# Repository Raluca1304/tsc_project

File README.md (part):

# PROIECT TSC OpenBook 
## Nica Mioara-Raluca 334CA 

---

## 1. Diagrama bloc

---

## 2. BOM (Bill Of Materials)

|   Nr. piesa | Nume piesa    | Site                                                                                                                                                                                                                                                | Datasheet                                                                                                                                                                |
|------------:|:--------------|:----------------------------------------------------------------------------------------------------------------------------------------------------------------------------------------------------------------------------------------------------|:-------------------------------------------------------------------------------------------------------------------------------------------------------------------------|
|           1 | BOOT_BUTON    | https://www.snapeda.com/parts/EVQP7L01P/Panasonic%20Electronic%20Components/view-part/?welcome=home                                                                                                                                                 | https://www.snapeda.com/parts/EVQP7L01P/Panasonic/datasheet/                                                                                                             |
|           2 | C1            | https://componentsearchengine.com/part-view/CC0402MRX5R5BB106/YAGEO                                                                                                                                                                                 | https://componentsearchengine.com/Datasheets/2/CC0402MRX5R5BB106.pdf                                                                                                     |
|           3 | C1_BAT        | https://componentsearchengine.com/part-view/CC0402MRX5R5BB106/YAGEO                                                                                                                                                                                 | https://componentsearchengine.com/Datasheets/2/CC0402MRX5R5BB106.pdf                                                                                                     |
|           4 | C1_BAT2       | https://componentsearchengine.com/part-view/CC0402MRX5R5BB106/YAGEO                                                                                                                                                                                 | https://componentsearchengine.com/Datasheets/2/CC0402MRX5R5BB106.pdf                                                                                                     |
|           5 | C2            | https://componentsearchengine.com/part-view/CC0402MRX5R5BB106/YAGEO                                                                                                                                                                                                                                                    |                                                                                                       |
|           6 | C2_BAT        | https://componentsearchengine.com/part-view/CC0402MRX5R5BB106/YAGEO                                                                                                                                                                                                                                                   |                                                                                                        |
|           7 | C3            | https://componentsearchengine.com/part-view/CC0402MRX5R5BB106/YAGEO                                                                                                                                                                                                                                                    |                                                                                                       |
|           8 | C4            | https://componentsearchengine.com/part-view/CC0402MRX5R5BB106/YAGEO                                                                                                                                                                                                                                                    |                                                                                                       |
|           9 | C4_USB        | https://componentsearchengine.com/part-view/CC0402MRX5R5BB106/YAGEO                                                                                                                                                                                                                                                    |                                                                                                       |
|          10 | C5            | https://componentsearchengine.com/part-view/CC0402MRX5R5BB106/YAGEO                                                                                                                                                                                                                                                    |                                                                                                       |
|          11 | C5_USB        | https://componentsearchengine.com/part-view/CC0402MRX5R5BB106/YAGEO                                                                                                                                                                                                                                                    |                                                                                                       |
|          12 | C6            | https://componentsearchengine.com/part-view/CC0402MRX5R5BB106/YAGEO                                                                                                                                                                                                                                                     |                                                                                                      |
|          13 | C7            | https://componentsearchengine.com/part-view/CC0402MRX5R5BB106/YAGEO                                                                                                                                                                                                                                                     |                                                                                                      |
|          14 | C8            | https://componentsearchengine.com/part-view/CC0402MRX5R5BB106/YAGEO                                                                                                                                                                                                                                                    |                                                                                                       |
|          15 | C9            | https://componentsearchengine.com/part-view/CC0402MRX5R5BB106/YAGEO                                                                                                                                                                                                                                                     |                                                                                                      |
|          16 | C10           | https://industry.panasonic.com/global/en/products/control/switch/light-touch/number/evqpuj02k                                                                                                                                                       | https://industry.panasonic.com/global/en/downloads?tab=catalog&small_g_cd=203&part_no=EVQPUJ02K                                                                          |
|          17 | C10_SUPERCAR  | https://industry.panasonic.com/global/en/products/control/switch/light-touch/number/evqpuj02k                                                                                                                                                       | https://industry.panasonic.com/global/en/downloads?tab=catalog&small_g_cd=203&part_no=EVQPUJ02K                                                                          |
|          18 | CHANGE_BUTTON | https://www.snapeda.com/parts/EVQP7L01P/Panasonic%20Electronic%20Components/view-part/?welcome=home                                                                                                                                                 | https://www.snapeda.com/parts/EVQP7L01P/Panasonic/datasheet/                                                                                                             |
|          19 | C_DELAY       | https://componentsearchengine.com/part-view/CC0402MRX5R5BB106/YAGEO                                                                                                                                                                                 | https://componentsearchengine.com/Datasheets/2/CC0402MRX5R5BB106.pdf                                                                                                     |
|          20 | D1            | https://www.snapeda.com/parts/USBLC6-2SC6Y/STMicroelectronics/view-part/?ref=eda                                                                                                                                                                    | https://www.snapeda.com/parts/USBLC6-2SC6Y/STMicroelectronics/view-part/?ref=eda                                                                                         |
|          21 | D2            | https://ro.mouser.com/ProductDetail/KYOCERA-AVX/SD0805S020S1R0?qs=jCA%252BPfw4LHbpkAoSnwrdjw%3D%3D                                                                                                                                                  | https://ro.mouser.com/datasheet/2/40/schottky-3165252.pdf                                                                                                                |
|          22 | D3            | https://ro.mouser.com/ProductDetail/KYOCERA-AVX/SD0805S020S1R0?qs=jCA%252BPfw4LHbpkAoSnwrdjw%3D%3D                                                                                                                                                                                                                                                     |                                                                       |
|          23 | D4            | https://ro.mouser.com/ProductDetail/KYOCERA-AVX/SD0805S020S1R0?qs=jCA%252BPfw4LHbpkAoSnwrdjw%3D%3D                                                                                                                                                                                                                                                    |                                                                        |
|          24 | D5            | https://ro.mouser.com/ProductDetail/KYOCERA-AVX/SD0805S020S1R0?qs=jCA%252BPfw4LHbpkAoSnwrdjw%3D%3D                                                                                                                                                                                                                                                     |                                                                       |
|          25 | D6            | https://www.snapeda.com/parts/PGB1010603MR/Littelfuse/view-part/?ref=eda                                                                                                                                                                            | https://www.snapeda.com/parts/PGB1010603MR/Littelfuse%20Inc./datasheet/                                                                                                  |
|          26 | D7            | https://ro.mouser.com/ProductDetail/KYOCERA-AVX/SD0805S020S1R0?qs=jCA%252BPfw4LHbpkAoSnwrdjw%3D%3D                                                                                                                                                  | https://ro.mouser.com/datasheet/2/40/schottky-3165252.pdf                                                                                                                |
|          27 | D8            | https://www.snapeda.com/parts/PGB1010603MR/Littelfuse/view-part/?ref=eda                                                                                                                                                                            | https://www.snapeda.com/parts/PGB1010603MR/Littelfuse%20Inc./datasheet/                                                                                                  |
|          28 | D9            | https://www.snapeda.com/parts/PGB1010603MR/Littelfuse/view-part/?ref=eda                                                                                                                                                                                                                                                   |                                                                                                   |
|          29 | D10           | https://www.snapeda.com/parts/PGB1010603MR/Littelfuse/view-part/?ref=eda                                                                                                                                                                                                                                                    |                                                                                                  |
|          30 | D11           | https://www.snapeda.com/parts/PGB1010603MR/Littelfuse/view-part/?ref=eda                                                                                                                                                                                                                                                     |                                                                                                 |
|          31 | D12           | https://www.snapeda.com/parts/PGB1010603MR/Littelfuse/view-part/?ref=eda                                                                                                                                                                                                                                                    |                                                                                                  |
|          32 | EPD_C1        | https://componentsearchengine.com/part-view/CC0402MRX5R5BB106/YAGEO                                                                                                                                                                                 | https://componentsearchengine.com/Datasheets/2/CC0402MRX5R5BB106.pdf                                                                                                     |
|          33 | EPD_C2        | https://componentsearchengine.com/part-view/CC0402MRX5R5BB106/YAGEO                                                                                                                                                                                 | https://componentsearchengine.com/Datasheets/2/CC0402MRX5R5BB106.pdf                                                                                                     |
|          34 | EPD_C5        | https://componentsearchengine.com/part-view/CC0402MRX5R5BB106/YAGEO                                                                                                                                                                                 | https://componentsearchengine.com/Datasheets/2/CC0402MRX5R5BB106.pdf                                                                                                     |
|          35 | EPD_C6        | https://componentsearchengine.com/part-view/CC0402MRX5R5BB106/YAGEO                                                                                                                                                                                 | https://componentsearchengine.com/Datasheets/2/CC0402MRX5R5BB106.pdf                                                                                                     |
|          36 | EPD_C7        | https://componentsearchengine.com/part-view/CC0402MRX5R5BB106/YAGEO                                                                                                                                                                                 | https://componentsearchengine.com/Datasheets/2/CC0402MRX5R5BB106.pdf                                                                                                     |
|          37 | EPD_C8        | https://componentsearchengine.com/part-view/CC0402MRX5R5BB106/YAGEO                                                                                                                                                                                 | https://componentsearchengine.com/Datasheets/2/CC0402MRX5R5BB106.pdf                                                                                                     |
|          38 | EPD_C9        | https://componentsearchengine.com/part-view/CC0402MRX5R5BB106/YAGEO                                                                                                                                                                                 | https://componentsearchengine.com/Datasheets/2/CC0402MRX5R5BB106.pdf                                                                                                     |
|          39 | EPD_C10       | https://componentsearchengine.com/part-view/CC0402MRX5R5BB106/YAGEO                                                                                                                                                                                 | https://componentsearchengine.com/Datasheets/2/CC0402MRX5R5BB106.pdf                                                                                                     |
|          40 | EPD_C11       | https://componentsearchengine.com/part-view/CC0402MRX5R5BB106/YAGEO                                                                                                                                                                                 | https://componentsearchengine.com/Datasheets/2/CC0402MRX5R5BB106.pdf                                                                                                     |
|          41 | EPD_C12       | https://componentsearchengine.com/part-view/CC0402MRX5R5BB106/YAGEO                                                                                                                                                                                 | https://componentsearchengine.com/Datasheets/2/CC0402MRX5R5BB106.pdf                                                                                                     |
|          42 | IC1           | https://componentsearchengine.com/part-view/BD5229G-TR/ROHM%20Semiconductor                                                                                                                                                                         | https://datasheet.datasheetarchive.com/originals/distributors/Datasheets_SAMA/f2b9741ef86007909f138d561a359946.pdf                                                       |
|          43 | IC4           | https://componentsearchengine.com/part-view/XC6220A331MR-G/Torex                                                                                                                                                                                    | https://product.torexsemi.com/system/files/series/xc6220.pdf                                                                                                             |
|          44 | J1            | https://componentsearchengine.com/part-view/FH34SRJ-24S-0.5SH(99)/Hirose                                                                                                                                                                            | https://www.hirose.com/en/product/document?clcode=CL0580-1255-6-99&productname=FH34SRJ-24S-0.5SH(99)&series=FH34SRJ&documenttype=2DDrawing&lang=en&documentid=0000990903 |
|          45 | J2            | https://componentsearchengine.com/part-view/USB4110-GF-A/GCT%20(GLOBAL%20CONNECTOR%20TECHNOLOGY)                                                                                                                                                    | https://gct.co/files/drawings/usb4110.pdf                                                                                                                                |
|          46 | J3            | https://www.snapeda.com/parts/PRT-14417/SparkFun/view-part/                                                                                                                                                                                         | https://www.snapeda.com/parts/PRT-14417/SparkFun%20Electronics/datasheet/                                                                                                |
|          47 | J4            | https://www.snapeda.com/parts/112A-TAAR-R03/Attend/view-part/                                                                                                                                                                                       | https://www.snapeda.com/parts/112A-TAAR-R03/Attend/datasheet/                                                                                                            |
|          48 | MCP73831      | https://ro.mouser.com/ProductDetail/Microchip-Technology/MCP73831T-2ACI-OT?qs=yUQqVecv4qvbBQBGbHx0Mw%3D%3D&utm_id=20109199409&utm_source=google&utm_medium=cpc&utm_marketing_tactic=emeacorp&gad_source=1&gbraid=0AAAAADn_wf0-USzm1eg1ywGvQg_qMgG3H | https://ro.mouser.com/datasheet/2/268/MCP73831_Family_Data_Sheet_DS20001984H-3441711.pdf                                                                                 |
|          49 | L1            | https://ro.mouser.com/ProductDetail/Wurth-Elektronik/744043680?qs=PGXP4M47uW6VkZq%252BkzjrHA%3D%3D                                                                                                                                                  | https://www.we-online.com/components/products/datasheet/744043680.pdf                                                                                                    |
|          50 | PFMF.050.1    | https://ro.mouser.com/ProductDetail/EPCOS-TDK/B72520T0350K062?qs=dEfas%2FXlABIszF52uu7vrg%3D%3D                                                                                                                                                     | https://www.tdk-electronics.tdk.com/inf/75/db/CTVS_14/Surge_protection_series.pdf                                                                                        |
|          51 | Q1            | https://componentsearchengine.com/part-view/DMG2305UX-7/Diodes%20Incorporated                                                                                                                                                                       | https://www.diodes.com//assets/Datasheets/DMG2305UX.pdf                                                                                                                  |
|          52 | Q2            | https://componentsearchengine.com/part-view/DMG2305UX-7/Diodes%20Incorporated                                                                                                                                                                                                                                                     |                                                                                            |
|          53 | Q3            | https://componentsearchengine.com/part-view/SI1308EDL-T1-GE3/Vishay                                                                                                                                                                                 | https://componentsearchengine.com/part-view/SI1308EDL-T1-GE3/Vishay                                                                                                      |
|          54 | R1            | https://componentsearchengine.com/part-view/R0402%201%25%20100%20K%20(RC0402FR-07100KL)/YAGEO                                                                                                                                                       | https://www.yageo.com/upload/media/product/products/datasheet/rchip/PYu-RC_Group_51_RoHS_L_12.pdf                                                                        |
|          55 | R1_PINH       | https://componentsearchengine.com/part-view/R0402%201%25%20100%20K%20(RC0402FR-07100KL)/YAGEO                                                                                                                                                       | https://www.yageo.com/upload/media/product/products/datasheet/rchip/PYu-RC_Group_51_RoHS_L_12.pdf                                                                        |
|          56 | R1_PINH1      | https://componentsearchengine.com/part-view/R0402%201%25%20100%20K%20(RC0402FR-07100KL)/YAGEO                                                                                                                                                       | https://www.yageo.com/upload/media/product/products/datasheet/rchip/PYu-RC_Group_51_RoHS_L_12.pdf                                                                        |
|          57 | R1_BAT        | https://componentsearchengine.com/part-view/R0402%201%25%20100%20K%20(RC0402FR-07100KL)/YAGEO                                                                                                                                                       | https://www.yageo.com/upload/media/product/products/datasheet/rchip/PYu-RC_Group_51_RoHS_L_12.pdf                                                                        |
|          58 | R1_PWRUSB     | https://componentsearchengine.com/part-view/R0402%201%25%20100%20K%20(RC0402FR-07100KL)/YAGEO                                                                                                                                                       | https://www.yageo.com/upload/media/product/products/datasheet/rchip/PYu-RC_Group_51_RoHS_L_12.pdf                                                                        |
|          59 | R2            | https://componentsearchengine.com/part-view/R0402%201%25%20100%20K%20(RC0402FR-07100KL)/YAGEO                                                            |                                                                                                                                                                          |
|          60 | R2_PINH       | https://componentsearchengine.com/part-view/R0402%201%25%20100%20K%20(RC0402FR-07100KL)/YAGEO                                                            |                                                                                                                                                                          |
|          61 | R2-PINH1      | https://componentsearchengine.com/part-view/R0402%201%25%20100%20K%20(RC0402FR-07100KL)/YAGEO                                                            |                                                                                                                                                                          |
|          62 | R2            | https://componentsearchengine.com/part-view/R0402%201%25%20100%20K%20(RC0402FR-07100KL)/YAGEO                                                            |                                                                                                                                                                          |
|          63 | R2-PINH       | https://componentsearchengine.com/part-view/R0402%201%25%20100%20K%20(RC0402FR-07100KL)/YAGEO                                                            |                                                                                                                                                                          |
|          64 | R2-PINH1      | https://componentsearchengine.com/part-view/R0402%201%25%20100%20K%20(RC0402FR-07100KL)/YAGEO                                                            |                                                                                                                                                                          |
|          65 | R2_USB        | https://componentsearchengine.com/part-view/R0402%201%25%20100%20K%20(RC0402FR-07100KL)/YAGEO                                                            |                                                                                                                                                                          |
|          66 | R2_USB        | https://componentsearchengine.com/part-view/R0402%201%25%20100%20K%20(RC0402FR-07100KL)/YAGEO                                                            |                                                                                                                                                                          |
|          67 | R2_USB1       | https://componentsearchengine.com/part-view/R0402%201%25%20100%20K%20(RC0402FR-07100KL)/YAGEO                                                            |                                                                                                                                                                          |
|          68 | R3            | https://componentsearchengine.com/part-view/R0402%201%25%20100%20K%20(RC0402FR-07100KL)/YAGEO                                                            |                                                                                                                                                                          |
|          69 | R4            | https://componentsearchengine.com/part-view/R0402%201%25%20100%20K%20(RC0402FR-07100KL)/YAGEO                                                            |                                                                                                                                                                          |
|          70 | R5            | https://componentsearchengine.com/part-view/R0402%201%25%20100%20K%20(RC0402FR-07100KL)/YAGEO                                                            |                                                                                                                                                                          |
|          71 | R6            | https://componentsearchengine.com/part-view/R0402%201%25%20100%20K%20(RC0402FR-07100KL)/YAGEO                                                            |                                                                                                                                                                          |
|          72 | R7            | https://componentsearchengine.com/part-view/R0402%201%25%20100%20K%20(RC0402FR-07100KL)/YAGEO                                                            |                                                                                                                                                                          |
|          73 | R8            | https://componentsearchengine.com/part-view/R0402%201%25%20100%20K%20(RC0402FR-07100KL)/YAGEO                                                            |                                                                                                                                                                          |
|          74 | R9            | https://componentsearchengine.com/part-view/R0402%201%25%20100%20K%20(RC0402FR-07100KL)/YAGEO                                                            |                                                                                                                                                                          |
|          75 | R10           | https://componentsearchengine.com/part-view/R0402%201%25%20100%20K%20(RC0402FR-07100KL)/YAGEO                                                            |                                                                                                                                                                          |
|          76 | RESET_BUTTON  | https://www.snapeda.com/parts/EVQP7L01P/Panasonic%20Electronic%20Components/view-part/?welcome=home                                                                                                                                                 | https://www.snapeda.com/parts/EVQP7L01P/Panasonic/datasheet/                                                                                                             |
|          77 | R_BOOT        | https://componentsearchengine.com/part-view/R0402%201%25%20100%20K%20(RC0402FR-07100KL)/YAGEO                                                                                                                                                       | https://www.yageo.com/upload/media/product/products/datasheet/rchip/PYu-RC_Group_51_RoHS_L_12.pdf                                                                        |
|          78 | R_CAPACITOR   | https://componentsearchengine.com/part-view/R0402%201%25%20100%20K%20(RC0402FR-07100KL)/YAGEO                                                                                                                                                       | https://www.yageo.com/upload/media/product/products/datasheet/rchip/PYu-RC_Group_51_RoHS_L_12.pdf                                                                        |
|          79 | R_CHANGE      | https://componentsearchengine.com/part-view/R0402%201%25%20100%20K%20(RC0402FR-07100KL)/YAGEO                                                                                                                                                       | https://www.yageo.com/upload/media/product/products/datasheet/rchip/PYu-RC_Group_51_RoHS_L_12.pdf                                                                        |
|          80 | R_CL1         | https://componentsearchengine.com/part-view/R0402%201%25%20100%20K%20(RC0402FR-07100KL)/YAGEO                                                                                                                                                       | https://www.yageo.com/upload/media/product/products/datasheet/rchip/PYu-RC_Group_51_RoHS_L_12.pdf                                                                        |
|          81 | R_RESET       | https://componentsearchengine.com/part-view/R0402%201%25%20100%20K%20(RC0402FR-07100KL)/YAGEO                                                                                                                                                       | https://www.yageo.com/upload/media/product/products/datasheet/rchip/PYu-RC_Group_51_RoHS_L_12.pdf                                                                        |
|          82 | SENSOR2       | https://www.snapeda.com/parts/BME680/Bosch/view-part/?welcome=home                                                                                                                                                                                  | https://www.snapeda.com/parts/BME680/Bosch%20Sensortec/datasheet/                                                                                                        |
|          83 | SJ1           | https://grabcad.com/library/solder-jumpers-1                                                                                                                                                                                                        | https://grabcad.com/library/solder-jumpers-1                                                                                                                             |
|          84 | TP1           | Am folosit aici model 3D personalizat realizat de mine                                                                                                                                                                                              |                                                                                                                                                                          |
|          85 | TP2           |                                                                                                                                                                                                                                                     |                                                                                                                                                                          |
|          86 | TP3           |                                                                                                                                                                                                                                                     |                                                                                                                                                                          |
|          87 | TP4           |                                                                                                                                                                                                                                                     |                                                                                                                                                                          |
|          88 | TP5           |                                                                                                                                                                                                                                                     |                                                                                                                                                                          |
|          89 | TP6           |                                                                                                                                                                                                                                                     |                                                                                                                                                                          |
|          90 | TP7           |                                                                                                                                                                                                                                                     |                                                                                                                                                                          |
|          91 | TP8           |                                                                                                                                                                                                                                                     |                                                                                                                                                                          |
|          92 | TP9           |                                                                                                                                                                                                                                                     |                                                                                                                                                                          |
|          93 | TP10          |                                                                                                                                                                                                                                                     |                                                                                                                                                                          |
|          94 | TP11          |                                                                                                                                                                                                                                                     |                                                                                                                                                                          |
|          95 | TP12          |                                                                                                                                                                                                                                                     |                                                                                                                                                                          |
|          96 | TP13          |                                                                                                                                                                                                                                                     |                                                                                                                                                                          |
|          97 | TP14          |                                                                                                                                                                                                                                                     |                                                                                                                                                                          |
|          98 | TP15          |                                                                                                                                                                                                                                                     |                                                                                                                                                                          |
|          99 | TP16          |                                                                                                                                                                                                                                                     |                                                                                                                                                                          |
|         100 | TP17          |                                                                                                                                                                                                                                                     |                                                                                                                                                                          |
|         101 | U1            | https://www.snapeda.com/parts/W25Q512JVEIQ/Winbond+Electronics/view-part/?ref=eda                                                                                                                                                                   | https://www.snapeda.com/parts/W25Q512JVEIQ/Winbond+Electronics/view-part/?ref=eda                                                                                        |
|         102 | U2            | https://www.snapeda.com/parts/ESP32-C6-WROOM-1-N8/Espressif+Systems/view-part/?ref=eda                                                                                                                                                              | https://www.snapeda.com/parts/ESP32-C6-WROOM-1-N8/Espressif%20Systems/datasheet/                                                                                         |
|         103 | U3            | https://www.snapeda.com/parts/DS3231SN%23/Analog+Devices/view-part/?ref=eda                                                                                                                                                                         | https://www.snapeda.com/parts/DS3231SN%23/Analog%20Devices/datasheet/                                                                                                    |
|         104 | U4            | https://www.snapeda.com/parts/MAX17048G+T10/Analog+Devices/view-part/?ref=eda                                                                                                                                                                       | https://www.snapeda.com/parts/MAX17048G+T10/Analog%20Devices/datasheet/                                                                                                  |

---

## 3. Descriere hardware

Proiectul OpenBook este un sistem portabil de monitorizare ambientala cu microcontroller ESP32-C6. Acesta comunica cu senzori, memorie externa si un ecran E-Ink pentru afisare. Dispozitivul este alimentat prin USB-C sau baterie Li-Po, avand management de energie eficient.

- ESP32-C6 WROOM este creierul central si comunica prin:
  - SPI: SD Card, Flash, E-Ink
  - I2C: BME688, RTC, MAX17048
  - UART: MH-Z19B, PMSA003
  - GPIO: butoane, test pads, control display

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
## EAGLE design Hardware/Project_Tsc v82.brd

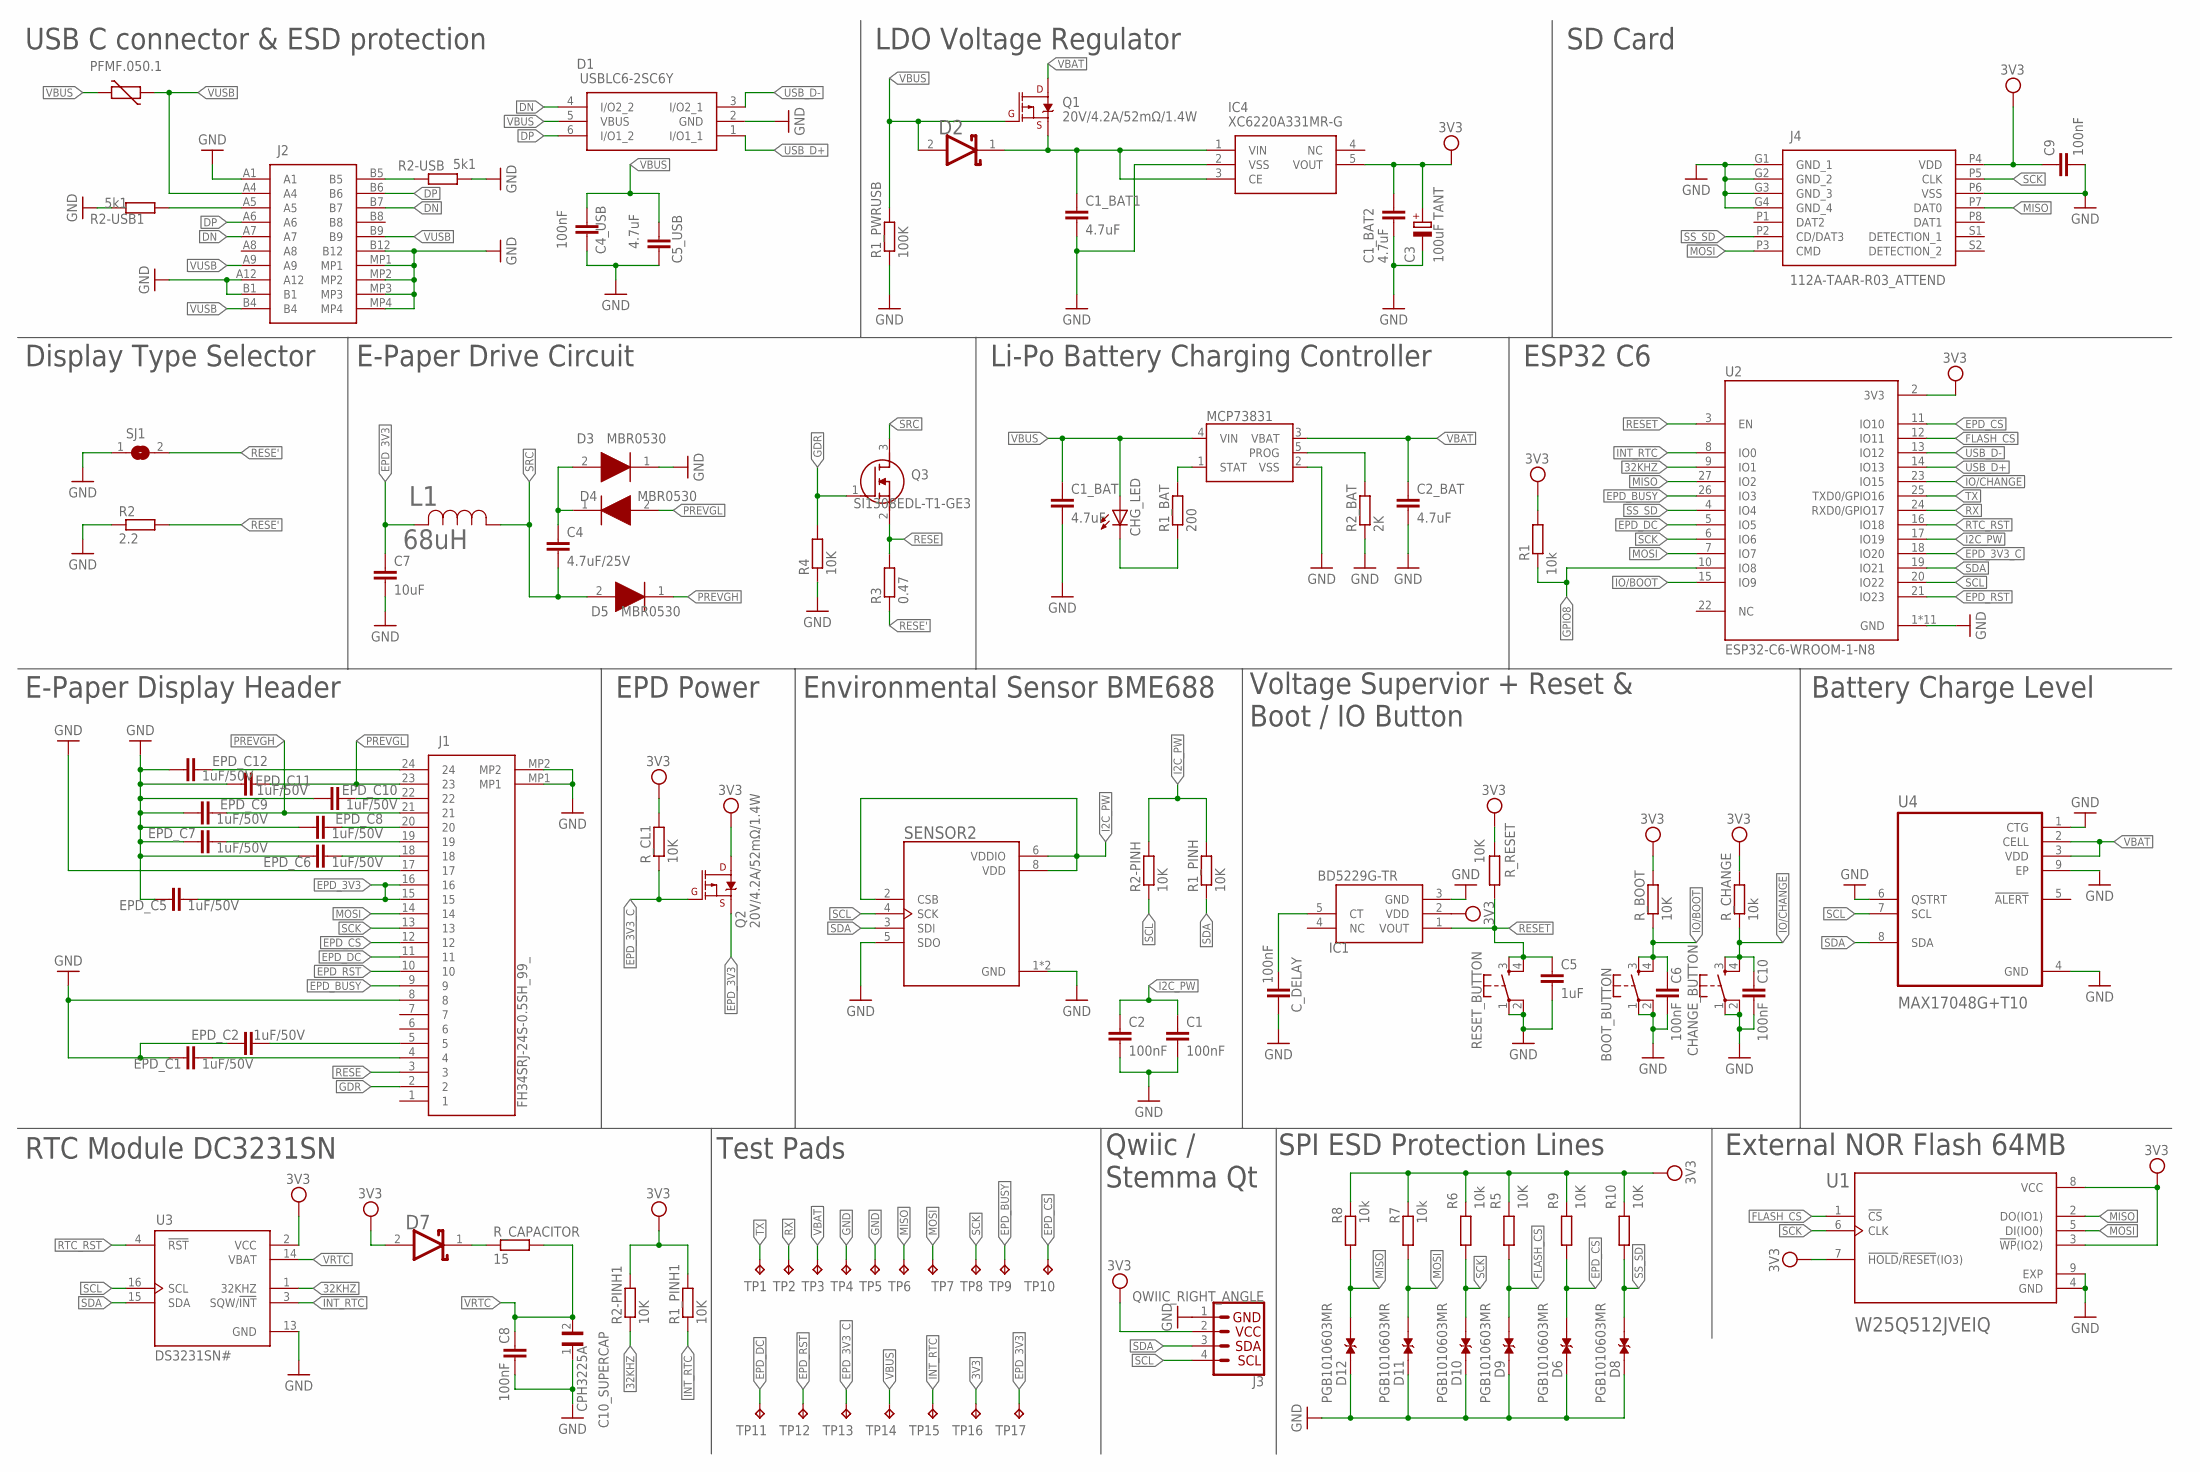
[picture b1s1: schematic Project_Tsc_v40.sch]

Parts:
BOOT_BUTTON: BUTTON_CUSYOMV1; MYBUTTON
C1, C2, C6, C9, C10: 100nF; EAGLE-LTSPICE_C0402
C1_BAT, C1_BAT1, C1_BAT2, C2_BAT, C5_USB: 4.7uF; ESP32_WROVER_EAGLE-LTSPICE_C0402
C3: 100uF TANT; RCL_CT3528
C4: 4.7uF/25V; ESP32_WROVER_EAGLE-LTSPICE_C0402
C4_USB, C8: 100nF; ESP32_WROVER_EAGLE-LTSPICE_C0402
C5: 1uF; EAGLE-LTSPICE_C0402
C7: 10uF; EAGLE-LTSPICE_C0402
C10_SUPERCAP: CPH3225A; CAPCP3225X100N
CHANGE_BUTTON: BUTTON_CUSYOMV1; MYBUTTON
CHG_LED: ADAFRUIT_LEDCHIP-LED0603; ADAFRUIT_CHIP-LED0603
C_DELAY: 100nF; ESP32_WROVER_EAGLE-LTSPICE_C0402
D1: USBLC6-2SC6Y; SOT95P280X145-6N
D2, D7: ESP32_WROVER_AVX---SD0805S020S1R0_AVX_SD0805S020S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; ESP32_WROVER_AVX---SD0805S020S1R0_AVX_SD0805S020S1R0_0
D3, D4, D5: MBR0530; SOD3716X135N
D6, D8, D9, D10, D11, D12: PGB1010603MR; DIOC1608X36N
EPD_C1, EPD_C2, EPD_C5, EPD_C6, EPD_C7, EPD_C8, EPD_C9, EPD_C10, EPD_C11, EPD_C12: 1uF/50V; EAGLE-LTSPICE_C0402
IC1: BD5229G-TR; SOT95P280X125-5N
IC4: XC6220A331MR-G; SOT95P280X120-5N
J1: FH34SRJ-24S-0.5SH_99_; FH34SRJ24S05SH99
J2: SAMACSYS_PARTS_USB4110-GF-A; SAMACSYS_PARTS_USB4110GFA
J3: QWIIC_RIGHT_ANGLE; JST04_1MM_RA
J4: 112A-TAAR-R03_ATTEND; 112ATAARR03ATTEND
L1: 68uH; IND_4828-WE-TPC_WRE
MCP73831: ESP32_WROVER_SPARKFUN-IC-POWER_MCP73831; ESP32_WROVER_SPARKFUN-IC-POWER_SOT23-5
PFMF.050.1: ESP32C6_VARISTORCN1812; ESP32C6_VARISTOR_CT/CN1812
Q1, Q2: 20V/4.2A/52mΩ/1.4W; ESP32_WROVER_SPARKFUN-DISCRETESEMI_SOT23-3
Q3: SI1308EDL-T1-GE3; SOT65P210X110-3N
R1, R6, R7, R8: 10k; ESP32_WROVER_EAGLE-LTSPICE_R0402
R1_BAT: 200; ESP32_WROVER_EAGLE-LTSPICE_R0402
R1_PINH, R1_PINH1, R2-PINH, R2-PINH1, R4, R5, R9, R10: 10K; ESP32_WROVER_EAGLE-LTSPICE_R0402
R1_PWRUSB: 100K; ESP32_WROVER_EAGLE-LTSPICE_R0402
R2: 2.2; ESP32_WROVER_EAGLE-LTSPICE_R0402
R2-USB, R2-USB1: 5k1; ESP32_WROVER_EAGLE-LTSPICE_R0402
R2_BAT: 2K; ESP32_WROVER_EAGLE-LTSPICE_R0402
R3: 0.47; ESP32_WROVER_EAGLE-LTSPICE_R0402
RESET_BUTTON: BUTTON_CUSYOMV1; MYBUTTON
R_BOOT: 10K; ESP32_WROVER_EAGLE-LTSPICE_R0402
R_CAPACITOR: 15; ESP32_WROVER_EAGLE-LTSPICE_R0402
R_CHANGE: 10k; ESP32_WROVER_EAGLE-LTSPICE_R0402
R_CL1: 10K; ESP32_WROVER_EAGLE-LTSPICE_R0402
R_RESET: 10K; ESP32_WROVER_EAGLE-LTSPICE_R0402
SENSOR2: ESP32_WROVER_BME680_BME680; ESP32_WROVER_BME680_PSON80P300X300X100-8N
SJ1: SJ
TP1, TP2, TP3, TP4, TP5, TP6, TP7, TP8, TP9, TP10, TP11, TP12, TP13, TP14, TP15, TP16, TP17: TPTP20R; TP20R
U1: W25Q512JVEIQ; SON127P600X800X80-9N
U2: ESP32-C6-WROOM-1-N8; XCVR_ESP32-C6-WROOM-1-N8
U3: DS3231SN#; SOIC127P1032X265-16N
U4: MAX17048G+T10; SON50P200X200X80-9N

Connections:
3V3: C1_BAT2.1, C3.+, C9.1, D7.2 (ANODE), IC1.2 (VDD), IC4.5 (VOUT), J3.2, J4.P4 (VDD), Q2.3 (D), R1.2, R1_PINH1.2, R2-PINH1.2, R5.2, R6.2, R7.2, R8.2, R9.2, R10.2, R_BOOT.2, R_CHANGE.2, R_CL1.2, R_RESET.2, TP16.TP, U1.3 (!WP!(IO2)), U1.7 (!HOLD!/!RESET!(IO3)), U1.8 (VCC), U2.2 (3V3), U3.2 (VCC)
32KHZ: R2-PINH1.1, U2.9 (IO1), U3.1 (32KHZ)
DN: D1.4 (I/O2_2), J2.A7, J2.B7
DP: D1.6 (I/O1_2), J2.A6, J2.B6
EPD_3V3: C7.1, EPD_C5.2, J1.15, J1.16, L1.2, Q2.2 (S), TP17.TP
EPD_3V3_C: Q2.1 (G), R_CL1.1, TP13.TP, U2.18 (IO20)
EPD_BUSY: J1.9, TP9.TP, U2.26 (IO3)
EPD_CS: D6.1, J1.12, R9.1, TP10.TP, U2.11 (IO10)
EPD_DC: J1.11, TP11.TP, U2.5 (IO5)
EPD_RST: J1.10, TP12.TP, U2.21 (IO23)
FLASH_CS: D9.1, R5.1, U1.1 (!CS), U2.12 (IO11)
GDR: J1.2, Q3.1 (G), R4.2
GND: BOOT_BUTTON.1, BOOT_BUTTON.2, C1.2, C1_BAT.2, C1_BAT1.2, C1_BAT2.2, C2.2, C2_BAT.2, C3.-, C4_USB.2, C5.2, C5_USB.2, C6.2, C7.2, C8.2, C9.2, C10.2, C10_SUPERCAP.1, CHANGE_BUTTON.1, CHANGE_BUTTON.2, C_DELAY.2, D1.2 (GND), D3.1 (K), D6.2, D8.2, D9.2, D10.2, D11.2, D12.2, EPD_C1.1, EPD_C2.1, EPD_C5.1, EPD_C6.1, EPD_C7.1, EPD_C8.1, EPD_C9.1, EPD_C10.1, EPD_C11.1, EPD_C12.1, IC1.3 (GND), IC4.2 (VSS), J1.8, J1.17, J1.MP1, J1.MP2, J2.A1, J2.A12, J2.B1, J2.B12, J2.MP1, J2.MP2, J2.MP3, J2.MP4, J3.1, J4.G1 (GND_1), J4.G2 (GND_2), J4.G3 (GND_3), J4.G4 (GND_4), J4.P6 (VSS), MCP73831.2 (VSS), R1_PWRUSB.1, R2.1, R2-USB.2, R2-USB1.1, R2_BAT.1, R4.1, RESET_BUTTON.1, RESET_BUTTON.2, SENSOR2.1 (GND), SENSOR2.5 (SDO), SENSOR2.7 (GND), SJ1.1, TP4.TP, TP5.TP, U1.4 (GND), U1.9 (EXP), U2.1 (GND), U2.28 (GND), U2.29_1 (GND), U2.29_2 (GND), U2.29_3 (GND), U2.29_4 (GND), U2.29_5 (GND), U2.29_6 (GND), U2.29_7 (GND), U2.29_8 (GND), U2.29_9 (GND), U3.13 (GND), U4.1 (CTG), U4.4 (GND), U4.6 (QSTRT), U4.9 (EP)
GPIO8: R1.1, U2.10 (IO8)
I2C_PW: C1.1, C2.1, R1_PINH.2, R2-PINH.2, SENSOR2.2 (CSB), SENSOR2.6 (VDDIO), SENSOR2.8 (VDD), U2.17 (IO19)
INT_RTC: R1_PINH1.1, TP15.TP, U2.8 (IO0), U3.3 (SQW/!INT)
IO/BOOT: BOOT_BUTTON.3, BOOT_BUTTON.4, C6.1, R_BOOT.1, U2.15 (IO9)
IO/CHANGE: C10.1, CHANGE_BUTTON.3, CHANGE_BUTTON.4, R_CHANGE.1, U2.23 (IO15)
MISO: D12.1, J4.P7 (DAT0), R8.1, TP6.TP, U1.2 (DO(IO1)), U2.27 (IO2)
MOSI: D11.1, J1.14, J4.P3 (CMD), R7.1, TP7.TP, U1.5 (DI(IO0)), U2.7 (IO7)
unnamed: J2.A5, R2-USB1.2
unnamed: J2.B5, R2-USB.1
unnamed: C1_BAT1.1, D2.1 (CATHODE), IC4.1 (VIN), IC4.3 (CE), Q1.2 (S)
unnamed: C4.1, D3.2 (A), D4.1 (K)
unnamed: EPD_C12.2, J1.24
unnamed: MCP73831.1 (STAT), R1_BAT.2
unnamed: CHG_LED.C, R1_BAT.1
unnamed: MCP73831.5 (PROG), R2_BAT.2
unnamed: C_DELAY.1, IC1.5 (CT)
unnamed: EPD_C10.2, J1.22
unnamed: EPD_C8.2, J1.20
unnamed: EPD_C7.2, J1.19
unnamed: EPD_C6.2, J1.18
unnamed: D7.1 (CATHODE), R_CAPACITOR.1
unnamed: EPD_C2.2, J1.5
unnamed: EPD_C1.2, J1.4
PREVGH: D5.1 (K), EPD_C9.2, J1.21
PREVGL: D4.2 (A), EPD_C11.2, J1.23
RESE: J1.3, Q3.2 (S), R3.2
RESE': R2.2, R3.1, SJ1.2
RESET: C5.1, IC1.1 (VOUT), RESET_BUTTON.3, RESET_BUTTON.4, R_RESET.1, U2.3 (EN)
RTC_RST: U2.16 (IO18), U3.4 (!RST)
RX: TP2.TP, U2.24 (RXD0/GPIO17)
SCK: D10.1, J1.13, J4.P5 (CLK), R6.1, TP8.TP, U1.6 (CLK), U2.6 (IO6)
SCL: J3.4, R2-PINH.1, SENSOR2.4 (SCK), U2.20 (IO22), U3.16 (SCL), U4.7 (SCL)
SDA: J3.3, R1_PINH.1, SENSOR2.3 (SDI), U2.19 (IO21), U3.15 (SDA), U4.8 (SDA)
SRC: C4.2, D5.2 (A), L1.1, Q3.3 (D)
SS_SD: D8.1, J4.P2 (CD/DAT3), R10.1, U2.4 (IO4)
TX: TP1.TP, U2.25 (TXD0/GPIO16)
USB_D+: D1.1 (I/O1_1), U2.14 (IO13)
USB_D-: D1.3 (I/O2_1), U2.13 (IO12)
VBAT: C2_BAT.1, MCP73831.3 (VBAT), Q1.3 (D), TP3.TP, U4.2 (CELL), U4.3 (VDD)
VBUS: C1_BAT.1, C4_USB.1, C5_USB.1, CHG_LED.A, D1.5 (VBUS), D2.2 (ANODE), MCP73831.4 (VIN), PFMF.050.1.2, Q1.1 (G), R1_PWRUSB.2, TP14.TP
VRTC: C8.1, C10_SUPERCAP.2, R_CAPACITOR.2, U3.14 (VBAT)
VUSB: J2.A4, J2.A9, J2.B4, J2.B9, PFMF.050.1.1

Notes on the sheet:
USB C connector & ESD protection
LDO Voltage Regulator
SD Card
Display Type Selector
E-Paper Drive Circuit
Li-Po Battery Charging Controller
ESP32 C6
E-Paper Display Header
EPD Power
Environmental Sensor BME688
Voltage Supervior + Reset & Boot / IO Button
Battery Charge Level
RTC Module DC3231SN
Test Pads
Qwiic / Stemma Qt
SPI ESD Protection Lines
External NOR Flash 64MB

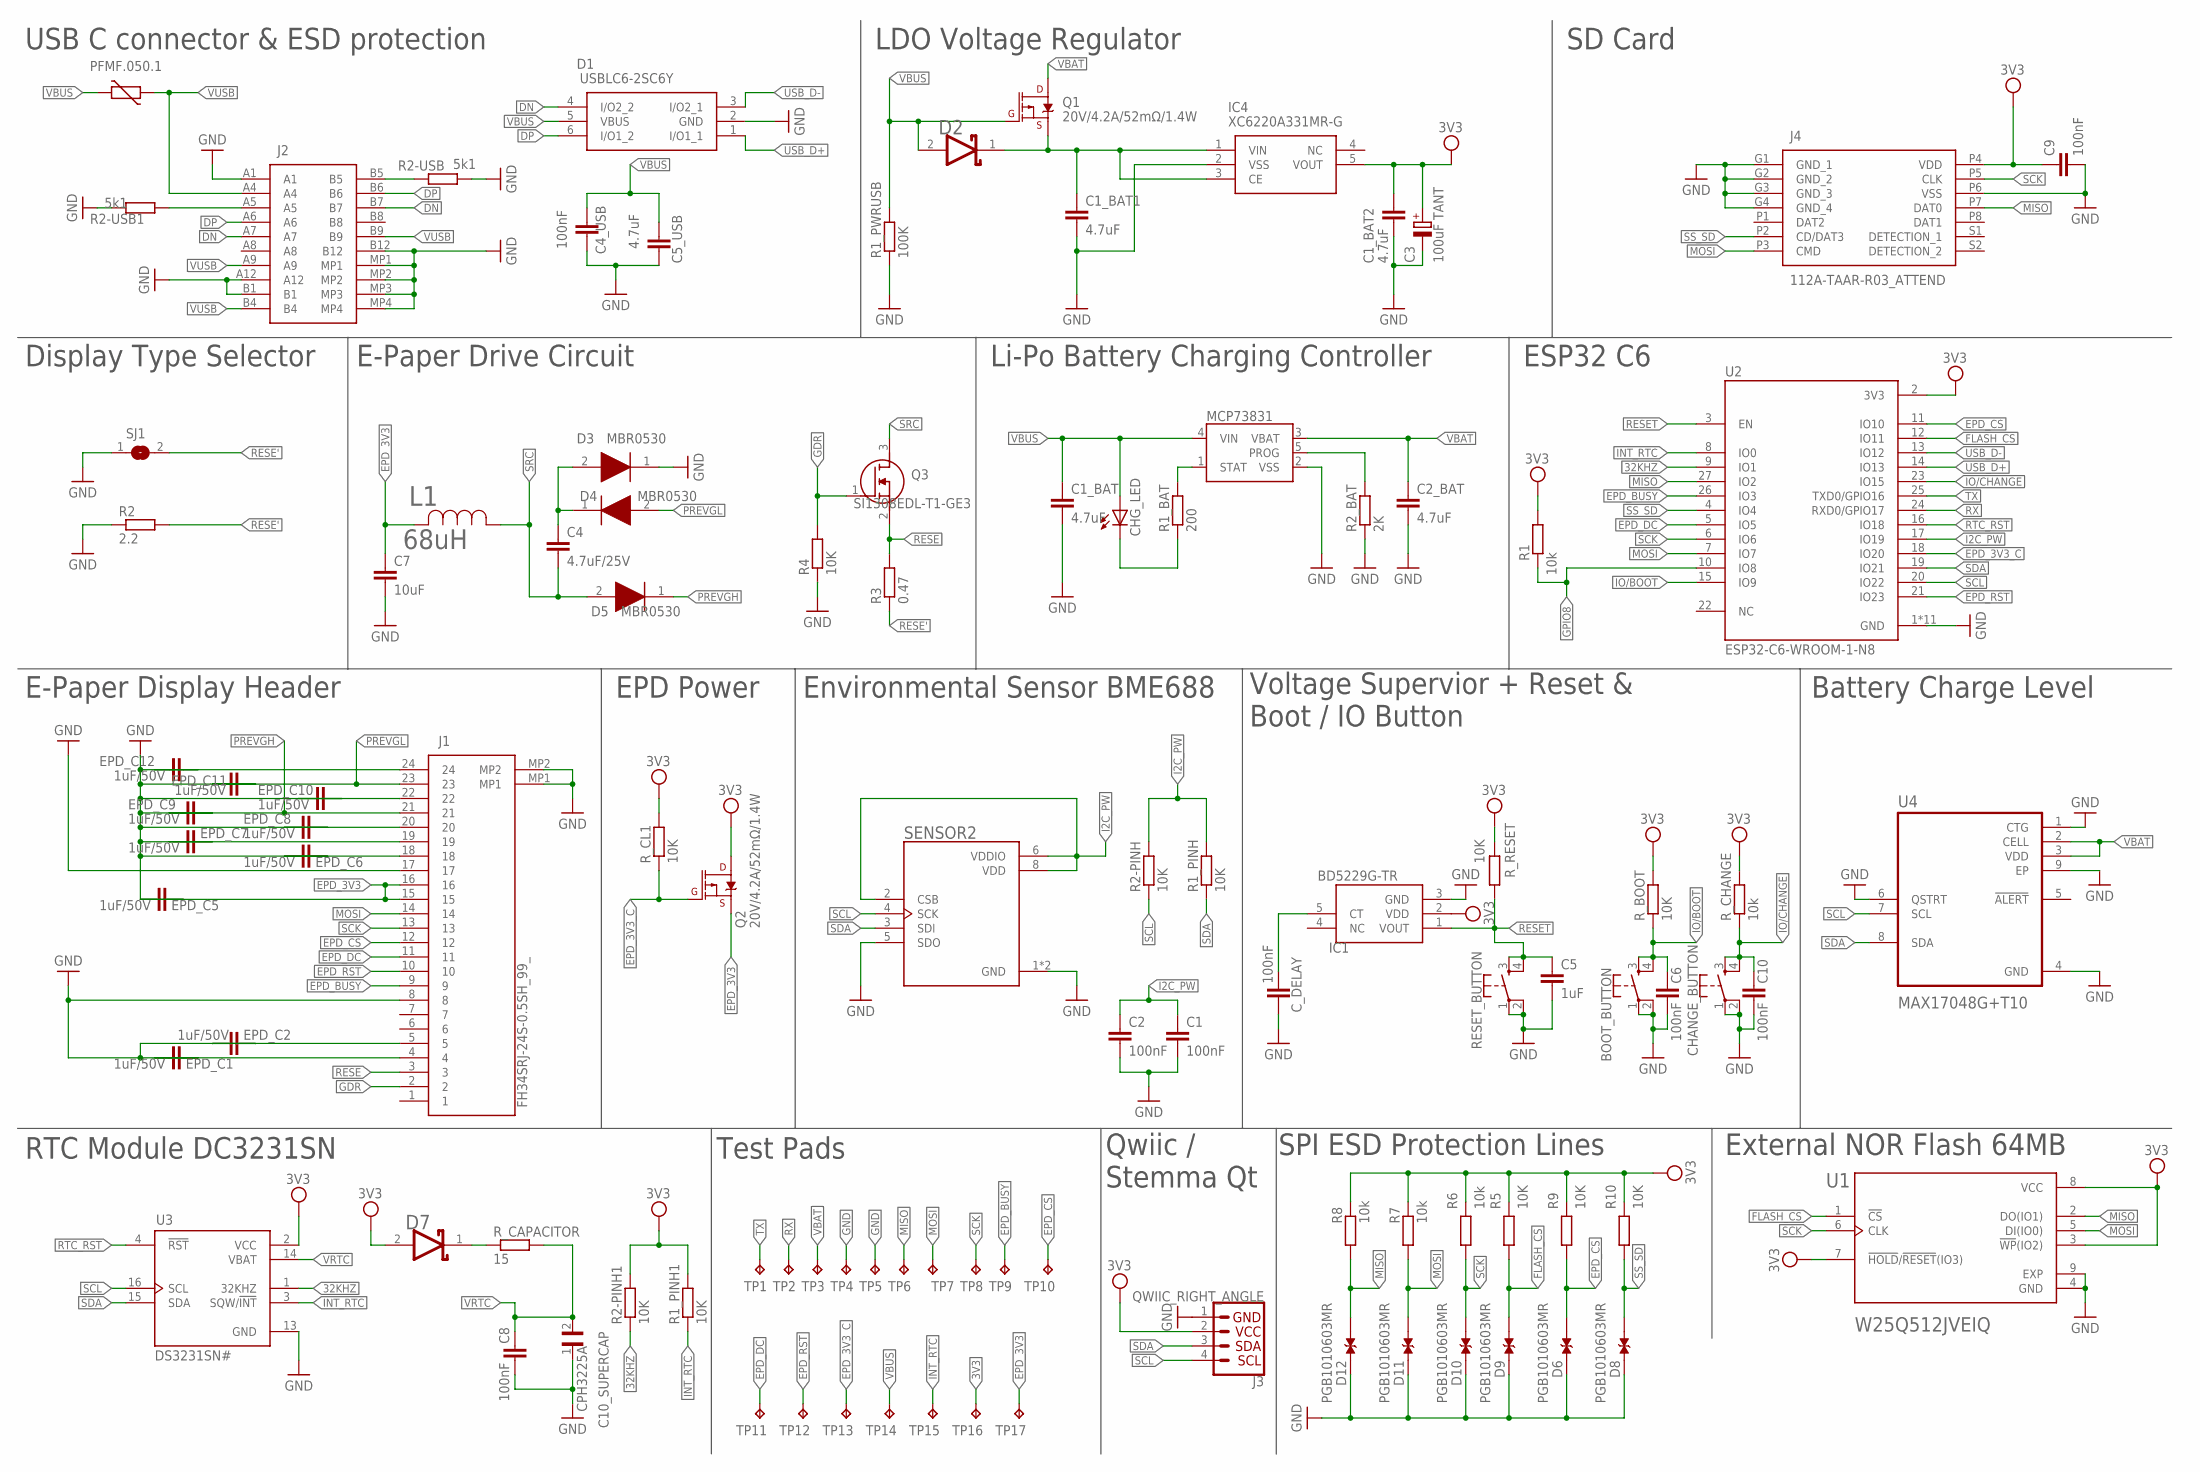
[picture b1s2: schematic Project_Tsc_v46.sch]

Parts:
BOOT_BUTTON: BUTTON_CUSYOMV1; MYBUTTON
C1, C2, C6, C9, C10: 100nF; EAGLE-LTSPICE_C0402
C1_BAT, C1_BAT1, C1_BAT2, C2_BAT, C5_USB: 4.7uF; ESP32_WROVER_EAGLE-LTSPICE_C0402
C3: 100uF TANT; RCL_CT3528
C4: 4.7uF/25V; ESP32_WROVER_EAGLE-LTSPICE_C0402
C4_USB, C8: 100nF; ESP32_WROVER_EAGLE-LTSPICE_C0402
C5: 1uF; EAGLE-LTSPICE_C0402
C7: 10uF; EAGLE-LTSPICE_C0402
C10_SUPERCAP: CPH3225A; CAPCP3225X100N
CHANGE_BUTTON: BUTTON_CUSYOMV1; MYBUTTON
CHG_LED: ADAFRUIT_LEDCHIP-LED0603; ADAFRUIT_CHIP-LED0603
C_DELAY: 100nF; ESP32_WROVER_EAGLE-LTSPICE_C0402
D1: USBLC6-2SC6Y; SOT95P280X145-6N
D2, D7: ESP32_WROVER_AVX---SD0805S020S1R0_AVX_SD0805S020S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; ESP32_WROVER_AVX---SD0805S020S1R0_AVX_SD0805S020S1R0_0
D3, D4, D5: MBR0530; SOD3716X135N
D6, D8, D9, D10, D11, D12: PGB1010603MR; DIOC1608X36N
EPD_C1, EPD_C2, EPD_C5, EPD_C6, EPD_C7, EPD_C8, EPD_C9, EPD_C10, EPD_C11, EPD_C12: 1uF/50V; EAGLE-LTSPICE_C0402
IC1: BD5229G-TR; SOT95P280X125-5N
IC4: XC6220A331MR-G; SOT95P280X120-5N
J1: FH34SRJ-24S-0.5SH_99_; FH34SRJ24S05SH99
J2: SAMACSYS_PARTS_USB4110-GF-A; SAMACSYS_PARTS_USB4110GFA
J3: QWIIC_RIGHT_ANGLE; JST04_1MM_RA
J4: 112A-TAAR-R03_ATTEND; 112ATAARR03ATTEND
L1: 68uH; IND_4828-WE-TPC_WRE
MCP73831: ESP32_WROVER_SPARKFUN-IC-POWER_MCP73831; ESP32_WROVER_SPARKFUN-IC-POWER_SOT23-5
PFMF.050.1: ESP32C6_VARISTORCN1812; ESP32C6_VARISTOR_CT/CN1812
Q1, Q2: 20V/4.2A/52mΩ/1.4W; ESP32_WROVER_SPARKFUN-DISCRETESEMI_SOT23-3
Q3: SI1308EDL-T1-GE3; SOT65P210X110-3N
R1, R6, R7, R8: 10k; ESP32_WROVER_EAGLE-LTSPICE_R0402
R1_BAT: 200; ESP32_WROVER_EAGLE-LTSPICE_R0402
R1_PINH, R1_PINH1, R2-PINH, R2-PINH1, R4, R5, R9, R10: 10K; ESP32_WROVER_EAGLE-LTSPICE_R0402
R1_PWRUSB: 100K; ESP32_WROVER_EAGLE-LTSPICE_R0402
R2: 2.2; ESP32_WROVER_EAGLE-LTSPICE_R0402
R2-USB, R2-USB1: 5k1; ESP32_WROVER_EAGLE-LTSPICE_R0402
R2_BAT: 2K; ESP32_WROVER_EAGLE-LTSPICE_R0402
R3: 0.47; ESP32_WROVER_EAGLE-LTSPICE_R0402
RESET_BUTTON: BUTTON_CUSYOMV1; MYBUTTON
R_BOOT: 10K; ESP32_WROVER_EAGLE-LTSPICE_R0402
R_CAPACITOR: 15; ESP32_WROVER_EAGLE-LTSPICE_R0402
R_CHANGE: 10k; ESP32_WROVER_EAGLE-LTSPICE_R0402
R_CL1: 10K; ESP32_WROVER_EAGLE-LTSPICE_R0402
R_RESET: 10K; ESP32_WROVER_EAGLE-LTSPICE_R0402
SENSOR2: ESP32_WROVER_BME680_BME680; ESP32_WROVER_BME680_PSON80P300X300X100-8N
SJ1: SJ
TP1, TP2, TP3, TP4, TP5, TP6, TP7, TP8, TP9, TP10, TP11, TP12, TP13, TP14, TP15, TP16, TP17: TPTP20R; TP20R
U1: W25Q512JVEIQ; SON127P600X800X80-9N
U2: ESP32-C6-WROOM-1-N8; XCVR_ESP32-C6-WROOM-1-N8
U3: DS3231SN#; SOIC127P1032X265-16N
U4: MAX17048G+T10; SON50P200X200X80-9N

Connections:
3V3: C1_BAT2.1, C3.+, C9.1, D7.2 (ANODE), IC1.2 (VDD), IC4.5 (VOUT), J3.2, J4.P4 (VDD), Q2.3 (D), R1.2, R1_PINH1.2, R2-PINH1.2, R5.2, R6.2, R7.2, R8.2, R9.2, R10.2, R_BOOT.2, R_CHANGE.2, R_CL1.2, R_RESET.2, TP16.TP, U1.3 (!WP!(IO2)), U1.7 (!HOLD!/!RESET!(IO3)), U1.8 (VCC), U2.2 (3V3), U3.2 (VCC)
32KHZ: R2-PINH1.1, U2.9 (IO1), U3.1 (32KHZ)
DN: D1.4 (I/O2_2), J2.A7, J2.B7
DP: D1.6 (I/O1_2), J2.A6, J2.B6
EPD_3V3: C7.1, EPD_C5.2, J1.15, J1.16, L1.2, Q2.2 (S), TP17.TP
EPD_3V3_C: Q2.1 (G), R_CL1.1, TP13.TP, U2.18 (IO20)
EPD_BUSY: J1.9, TP9.TP, U2.26 (IO3)
EPD_CS: D6.1, J1.12, R9.1, TP10.TP, U2.11 (IO10)
EPD_DC: J1.11, TP11.TP, U2.5 (IO5)
EPD_RST: J1.10, TP12.TP, U2.21 (IO23)
FLASH_CS: D9.1, R5.1, U1.1 (!CS), U2.12 (IO11)
GDR: J1.2, Q3.1 (G), R4.2
GND: BOOT_BUTTON.1, BOOT_BUTTON.2, C1.2, C1_BAT.2, C1_BAT1.2, C1_BAT2.2, C2.2, C2_BAT.2, C3.-, C4_USB.2, C5.2, C5_USB.2, C6.2, C7.2, C8.2, C9.2, C10.2, C10_SUPERCAP.1, CHANGE_BUTTON.1, CHANGE_BUTTON.2, C_DELAY.2, D1.2 (GND), D3.1 (K), D6.2, D8.2, D9.2, D10.2, D11.2, D12.2, EPD_C1.1, EPD_C2.1, EPD_C5.1, EPD_C6.1, EPD_C7.1, EPD_C8.1, EPD_C9.1, EPD_C10.1, EPD_C11.1, EPD_C12.1, IC1.3 (GND), IC4.2 (VSS), J1.8, J1.17, J1.MP1, J1.MP2, J2.A1, J2.A12, J2.B1, J2.B12, J2.MP1, J2.MP2, J2.MP3, J2.MP4, J3.1, J4.G1 (GND_1), J4.G2 (GND_2), J4.G3 (GND_3), J4.G4 (GND_4), J4.P6 (VSS), MCP73831.2 (VSS), R1_PWRUSB.1, R2.1, R2-USB.2, R2-USB1.1, R2_BAT.1, R4.1, RESET_BUTTON.1, RESET_BUTTON.2, SENSOR2.1 (GND), SENSOR2.5 (SDO), SENSOR2.7 (GND), SJ1.1, TP4.TP, TP5.TP, U1.4 (GND), U1.9 (EXP), U2.1 (GND), U2.28 (GND), U2.29_1 (GND), U2.29_2 (GND), U2.29_3 (GND), U2.29_4 (GND), U2.29_5 (GND), U2.29_6 (GND), U2.29_7 (GND), U2.29_8 (GND), U2.29_9 (GND), U3.13 (GND), U4.1 (CTG), U4.4 (GND), U4.6 (QSTRT), U4.9 (EP)
GPIO8: R1.1, U2.10 (IO8)
I2C_PW: C1.1, C2.1, R1_PINH.2, R2-PINH.2, SENSOR2.2 (CSB), SENSOR2.6 (VDDIO), SENSOR2.8 (VDD), U2.17 (IO19)
INT_RTC: R1_PINH1.1, TP15.TP, U2.8 (IO0), U3.3 (SQW/!INT)
IO/BOOT: BOOT_BUTTON.3, BOOT_BUTTON.4, C6.1, R_BOOT.1, U2.15 (IO9)
IO/CHANGE: C10.1, CHANGE_BUTTON.3, CHANGE_BUTTON.4, R_CHANGE.1, U2.23 (IO15)
MISO: D12.1, J4.P7 (DAT0), R8.1, TP6.TP, U1.2 (DO(IO1)), U2.27 (IO2)
MOSI: D11.1, J1.14, J4.P3 (CMD), R7.1, TP7.TP, U1.5 (DI(IO0)), U2.7 (IO7)
unnamed: J2.A5, R2-USB1.2
unnamed: J2.B5, R2-USB.1
unnamed: C1_BAT1.1, D2.1 (CATHODE), IC4.1 (VIN), IC4.3 (CE), Q1.2 (S)
unnamed: C4.1, D3.2 (A), D4.1 (K)
unnamed: EPD_C12.2, J1.24
unnamed: MCP73831.1 (STAT), R1_BAT.2
unnamed: CHG_LED.C, R1_BAT.1
unnamed: MCP73831.5 (PROG), R2_BAT.2
unnamed: C_DELAY.1, IC1.5 (CT)
unnamed: EPD_C10.2, J1.22
unnamed: EPD_C8.2, J1.20
unnamed: EPD_C7.2, J1.19
unnamed: EPD_C6.2, J1.18
unnamed: D7.1 (CATHODE), R_CAPACITOR.1
unnamed: EPD_C2.2, J1.5
unnamed: EPD_C1.2, J1.4
PREVGH: D5.1 (K), EPD_C9.2, J1.21
PREVGL: D4.2 (A), EPD_C11.2, J1.23
RESE: J1.3, Q3.2 (S), R3.2
RESE': R2.2, R3.1, SJ1.2
RESET: C5.1, IC1.1 (VOUT), RESET_BUTTON.3, RESET_BUTTON.4, R_RESET.1, U2.3 (EN)
RTC_RST: U2.16 (IO18), U3.4 (!RST)
RX: TP2.TP, U2.24 (RXD0/GPIO17)
SCK: D10.1, J1.13, J4.P5 (CLK), R6.1, TP8.TP, U1.6 (CLK), U2.6 (IO6)
SCL: J3.4, R2-PINH.1, SENSOR2.4 (SCK), U2.20 (IO22), U3.16 (SCL), U4.7 (SCL)
SDA: J3.3, R1_PINH.1, SENSOR2.3 (SDI), U2.19 (IO21), U3.15 (SDA), U4.8 (SDA)
SRC: C4.2, D5.2 (A), L1.1, Q3.3 (D)
SS_SD: D8.1, J4.P2 (CD/DAT3), R10.1, U2.4 (IO4)
TX: TP1.TP, U2.25 (TXD0/GPIO16)
USB_D+: D1.1 (I/O1_1), U2.14 (IO13)
USB_D-: D1.3 (I/O2_1), U2.13 (IO12)
VBAT: C2_BAT.1, MCP73831.3 (VBAT), Q1.3 (D), TP3.TP, U4.2 (CELL), U4.3 (VDD)
VBUS: C1_BAT.1, C4_USB.1, C5_USB.1, CHG_LED.A, D1.5 (VBUS), D2.2 (ANODE), MCP73831.4 (VIN), PFMF.050.1.2, Q1.1 (G), R1_PWRUSB.2, TP14.TP
VRTC: C8.1, C10_SUPERCAP.2, R_CAPACITOR.2, U3.14 (VBAT)
VUSB: J2.A4, J2.A9, J2.B4, J2.B9, PFMF.050.1.1

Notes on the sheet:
USB C connector & ESD protection
LDO Voltage Regulator
SD Card
Display Type Selector
E-Paper Drive Circuit
Li-Po Battery Charging Controller
ESP32 C6
E-Paper Display Header
EPD Power
Environmental Sensor BME688
Voltage Supervior + Reset & Boot / IO Button
Battery Charge Level
RTC Module DC3231SN
Test Pads
Qwiic / Stemma Qt
SPI ESD Protection Lines
External NOR Flash 64MB

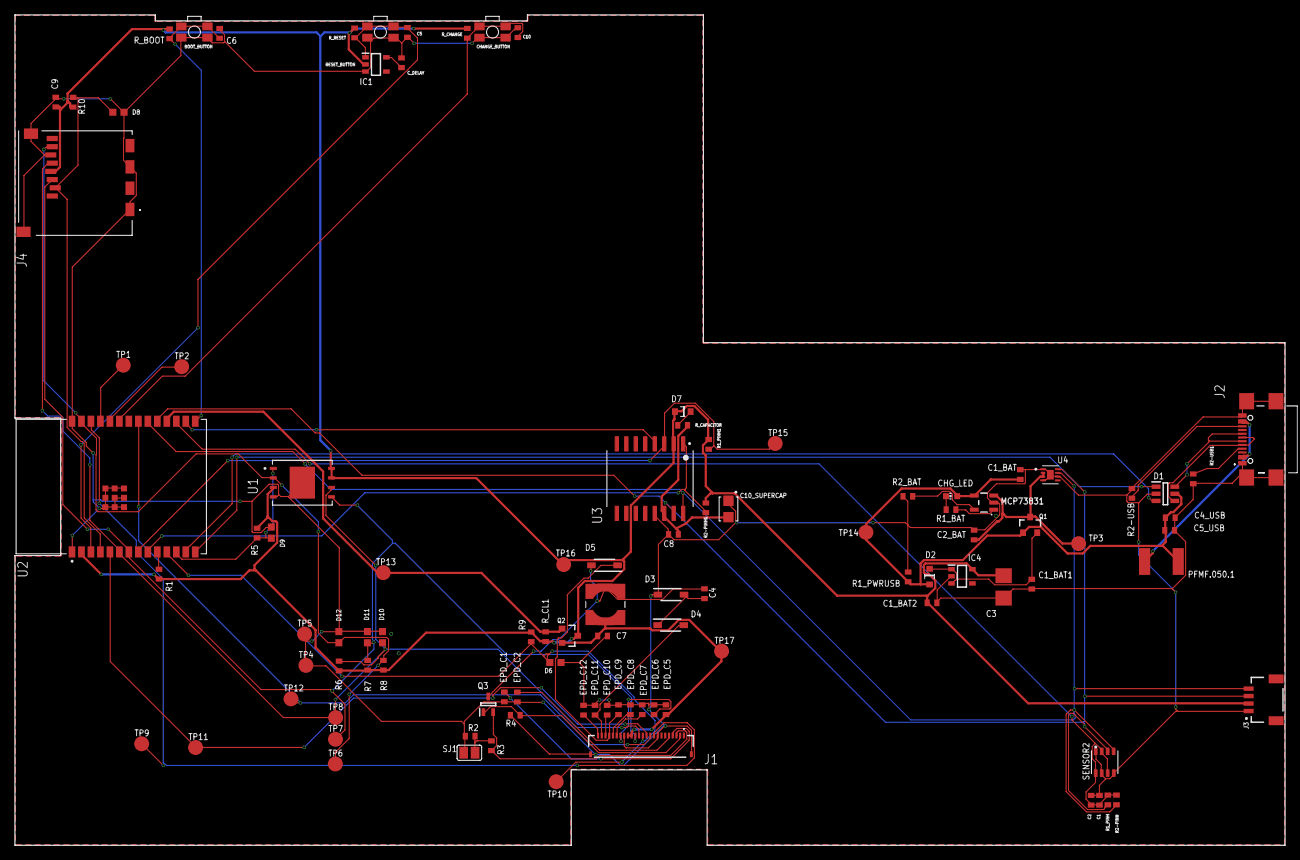
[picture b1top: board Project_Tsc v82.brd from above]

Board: 2 copper layers, 170.1 x 111.2 mm, 103 parts (0 on the bottom side), 55 nets.

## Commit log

2025-04-06 Create LICENSE

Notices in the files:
parts and their libraries:
COPYRIGHT: Copyright (C) 2024 Ultra Librarian. All rights reserved.
